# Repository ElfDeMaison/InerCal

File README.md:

# InerCal – Système de calcul du moment d'inertie embarqué

**InerCal** est un système embarqué destiné à mesurer le **moment d'inertie d'un objet** à l'aide d'un **balancier à deux fils**. Il s’appuie sur une carte **ESP32** et embarque une interface web accessible en Wi-Fi. Le système permet de récupérer les données de mesure directement via un navigateur web sans besoin de logiciel externe.

---

## Objectif

Le but du projet est de fournir un outil **simple, autonome et portable** pour estimer le moment d'inertie d'objets à partir des oscillations d’un système pendulaire.

Le système :

- enregistre les oscillations via un capteur (type ICM-42688),
- envoie les données sur un serveur web embarqué dans l’ESP32,
- affiche les mesures sur une **interface web responsive**.

---

## Matériel requis

- 1x **ESP32** (WROOM ou équivalent)
- 1x **Capteur inertiel** (ex. ICM-42688 via SPI ou I2C)

---

## Guide d'utilisation 

Voici les étapes à suivre pour utiliser le système **InerCal** avec un objet réel :

### Installation physique

1. **Fixer l’InerCal** solidement sur l’objet dont vous souhaitez mesurer le moment d'inertie.

2. **Allumer l’ESP32** (via USB ou batterie).

---

### Connexion et interface

3. **Se connecter au Wi-Fi** de l’ESP32 (point d’accès créé automatiquement).

4. Ouvrir un navigateur et accéder à l’interface via l’adresse IP indiquée dans le moniteur série (ou adresse par défaut, souvent `192.168.4.1`).

---

### Mesure du moment d'inertie

5. **Calibrer le gyroscope** en cliquant sur le bouton **"Calibrer le gyroscope"**.

6. Cliquer sur **"Démarrer"** pour lancer la capture des données.

7. **Faire osciller l’objet** autour de son axe de rotation.

8. Une fois les oscillations terminées, cliquer sur **"Arrêter"**.

---

### Analyse des données

9. **Remplir les champs physiques** dans l’interface (masse, distance, etc.).

10. Cliquer sur **"Télécharger les données"** → un fichier `.json` est enregistré.

---

### Post-traitement avec Python

11. Lancer le script Python d’analyse :

```bash
python analyse.py

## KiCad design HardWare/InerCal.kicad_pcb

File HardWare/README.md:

# InerCal HardWare

microcontroleur = [XIAO-ESP32-C3 seeed studio](https://wiki.seeedstudio.com/XIAO_ESP32C3_Getting_Started/)

IMU = ICM42688-P

Library KiCad = https://github.com/MGRZ31/Kicad_Libraries_GRZ

TODO : Le signal MISO a ete deplacé du GPIO9 au GPIO20 car cela empêche l'esp32 de démarrer correctement

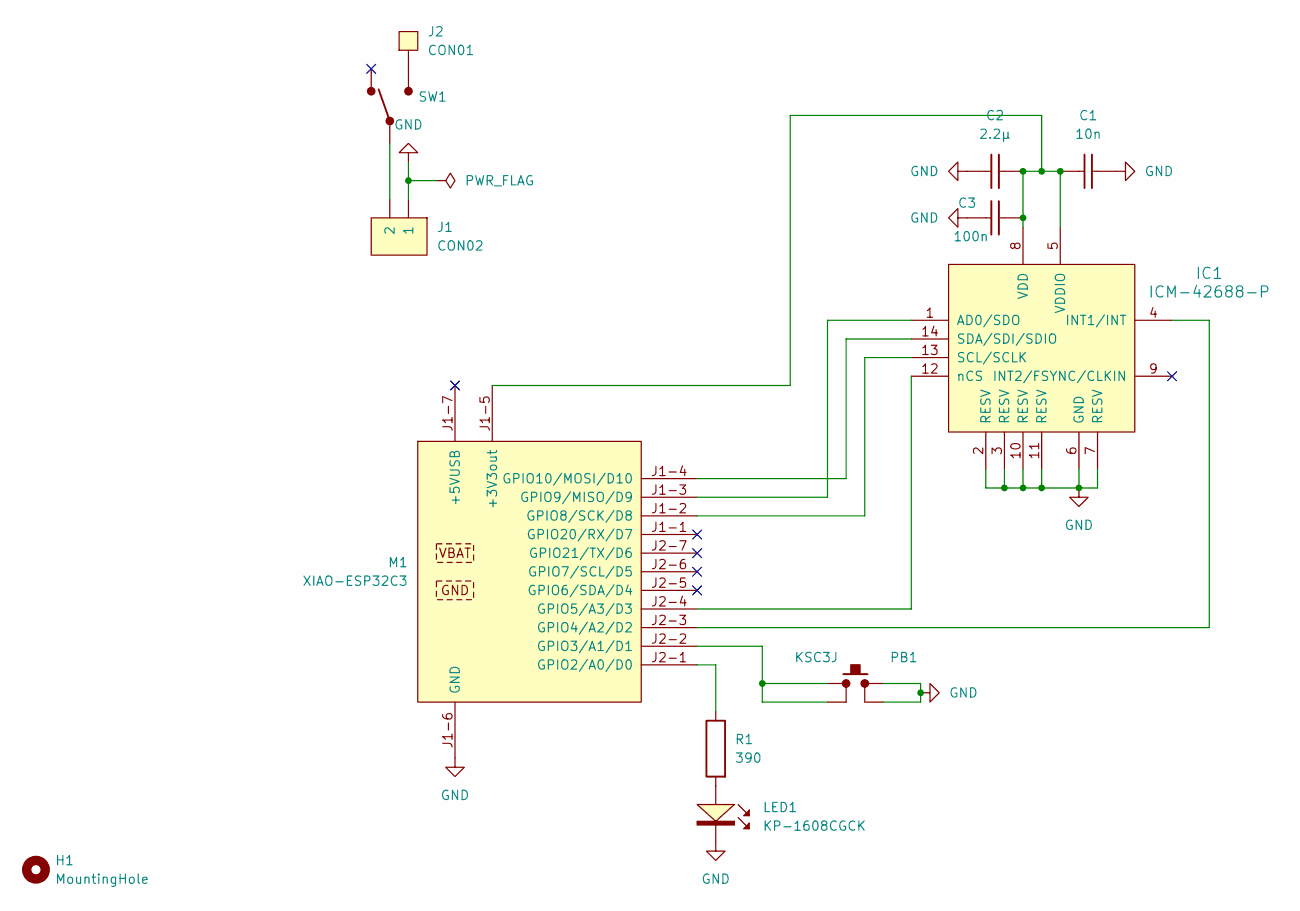
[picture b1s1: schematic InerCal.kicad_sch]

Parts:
C1: 10n; C_0603
C2: 2.2µ; C_0603
C3: 100n; C_0603
H1: MountingHole; MountingHole_2.2mm_M2
IC1: ICM-42688-P
J1: CON02; PicoBlade_53261-0271
J2: CON01; SquareWirePad_SMD_2x4mm
LED1: KP-1608CGCK
M1: XIAO-ESP32C3; XIAO-ESP32C3_Socket_SMD
PB1: KSC3J
R1: 390; R_0603
SW1: 1K2; 1K2_90deg

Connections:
GND: C1.2, C2.1, C3.1, IC1.2 (RESV), IC1.3 (RESV), IC1.6 (GND), IC1.7 (RESV), IC1.10 (RESV), IC1.11 (RESV), J1.1, LED1.1 (K), M1.J1-6 (GND), PB1.2, PB1.3
unnamed: IC1.1 (AD0/SDO), M1.J1-3 (GPIO9/MISO/D9)
unnamed: IC1.4 (INT1/INT), M1.J2-3 (GPIO4/A2/D2)
unnamed: IC1.13 (SCL/SCLK), M1.J1-2 (GPIO8/SCK/D8)
unnamed: IC1.14 (SDA/SDI/SDIO), M1.J1-4 (GPIO10/MOSI/D10)
unnamed: C1.1, C2.2, C3.2, IC1.5 (VDDIO), IC1.8 (VDD), M1.J1-5 (+3V3out)
unnamed: IC1.12 (nCS), M1.J2-4 (GPIO5/A3/D3)
unnamed: J1.2, SW1.1
unnamed: J2.1, SW1.3
unnamed: LED1.2 (A), R1.1
unnamed: M1.J2-1 (GPIO2/A0/D0), R1.2
unnamed: M1.J2-2 (GPIO3/A1/D1), PB1.1, PB1.4

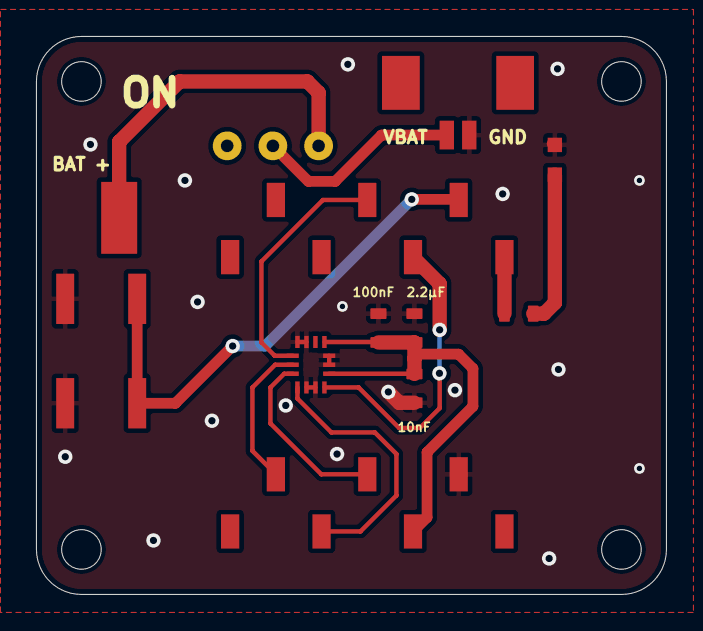
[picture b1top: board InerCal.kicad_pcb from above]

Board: 2 copper layers, 35.0 x 31.0 mm, 15 parts (0 on the bottom side), 12 nets.

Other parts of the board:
H1#2, H1#3, H1#4: MountingHole; MountingHole_2.2mm_M2

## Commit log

2025-05-26 add requirements.txt
2025-05-26 add README hardWare
2025-05-26 add README FirmWare
2025-05-27 update Index
